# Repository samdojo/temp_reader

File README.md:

# Tempurature reader

This repo contains the schematic, code, and 3D print file to build a simple temperature reader

#### Software Dependencies
- Arduino library "adafruit_AM2320" v1.2.1

#### Materials List
- Arduino Nano
- 3 single-digit seven-segment displays (KW1-501CSB)
- Tempurature and humidity sensor (AM2320)
- 3 NPN Transistors (2N3904)
- 2 pull-up resistors (2.2-10KOhm)
- Servo (SG90)
- 4 female-to-female jumper wires
- 5 #2 1/4" screws
- glue

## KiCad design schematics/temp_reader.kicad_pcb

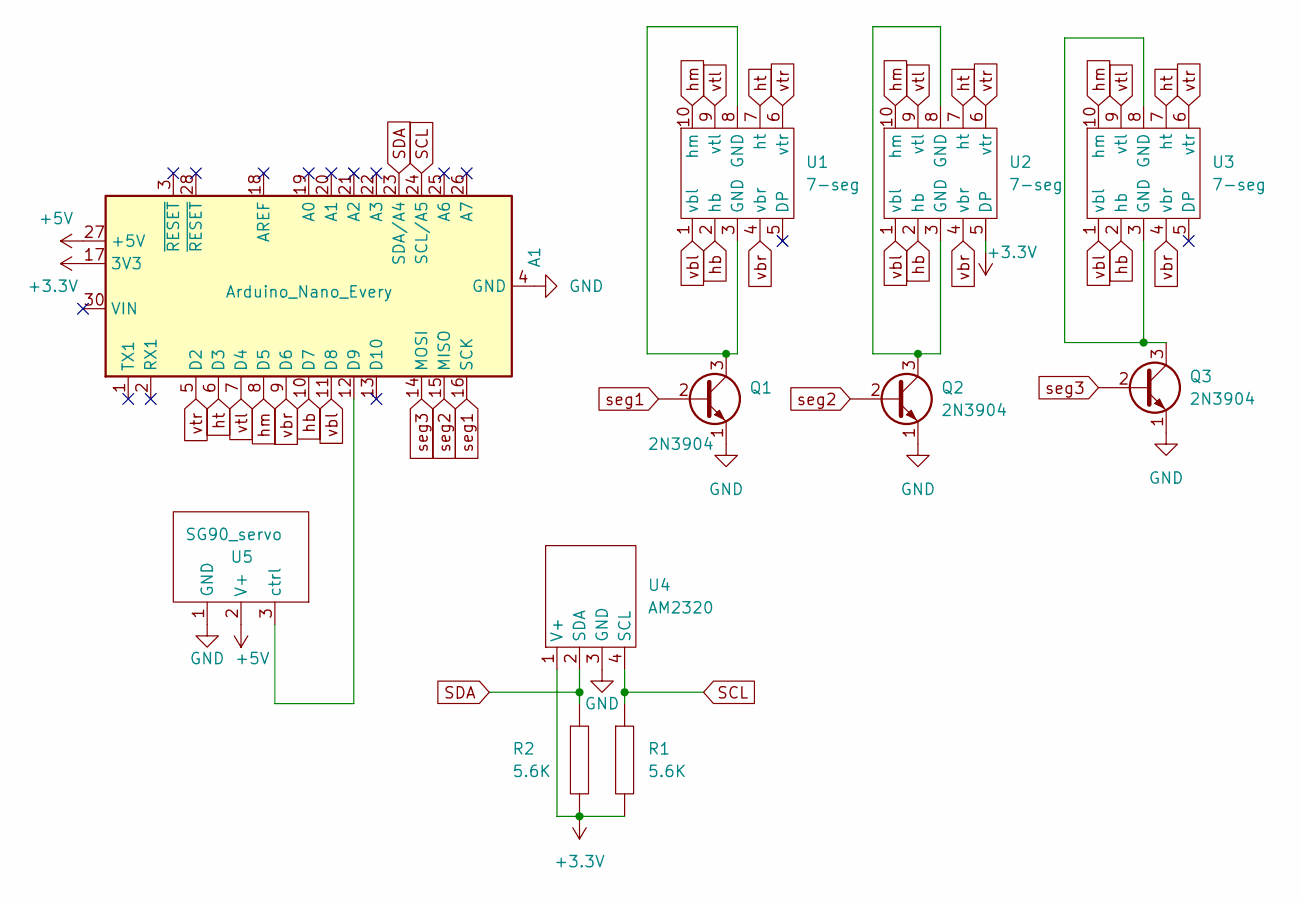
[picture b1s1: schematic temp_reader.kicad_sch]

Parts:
A1: Arduino_Nano_Every; Arduino_Nano
Q1, Q2, Q3: 2N3904; TO-92_Inline
R1, R2: 5.6K; resistor
U1, U2, U3: 7-seg; 7SegmentLED_LTS6760_LTS6780
U4: AM2320; AM2320 (temperature and humidity sensor)
U5: SG90_servo; MG90S servo

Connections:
+3.3V: A1.17 (3V3), R1.2, R2.2, U2.5 (DP), U4.1 (V+)
+5V: A1.27 (+5V), U5.2 (V+)
GND: A1.4 (GND), A1.29 (GND), Q1.1 (E), Q2.1 (E), Q3.1 (E), U4.3 (GND), U5.1 (GND)
unnamed: A1.12 (D9), U5.3 (ctrl)
unnamed: Q1.3 (C), U1.3 (GND), U1.8 (GND)
unnamed: Q2.3 (C), U2.3 (GND), U2.8 (GND)
unnamed: Q3.3 (C), U3.3 (GND), U3.8 (GND)
SCL: A1.24 (SCL/A5), R1.1, U4.4 (SCL)
SDA: A1.23 (SDA/A4), R2.1, U4.2 (SDA)
hb: A1.10 (D7), U1.2 (hb), U2.2 (hb), U3.2 (hb)
hm: A1.8 (D5), U1.10 (hm), U2.10 (hm), U3.10 (hm)
ht: A1.6 (D3), U1.7 (ht), U2.7 (ht), U3.7 (ht)
seg1: A1.16 (SCK), Q1.2 (B)
seg2: A1.15 (MISO), Q2.2 (B)
seg3: A1.14 (MOSI), Q3.2 (B)
vbl: A1.11 (D8), U1.1 (vbl), U2.1 (vbl), U3.1 (vbl)
vbr: A1.9 (D6), U1.4 (vbr), U2.4 (vbr), U3.4 (vbr)
vtl: A1.7 (D4), U1.9 (vtl), U2.9 (vtl), U3.9 (vtl)
vtr: A1.5 (D2), U1.6 (vtr), U2.6 (vtr), U3.6 (vtr)

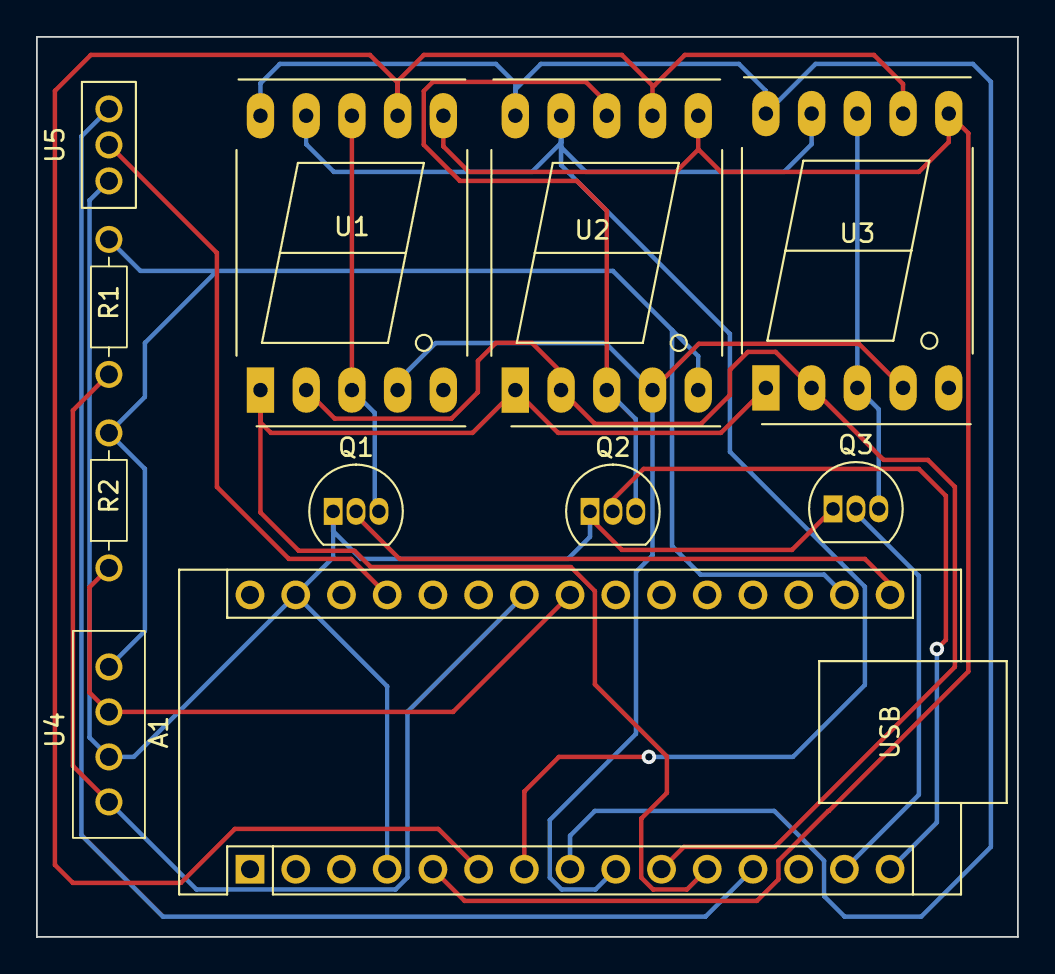
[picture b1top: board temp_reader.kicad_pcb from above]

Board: 2 copper layers, 54.5 x 50.0 mm, 11 parts (0 on the bottom side), 19 nets.

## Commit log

2023-02-24 initial
2023-02-26 added schematic picture
2023-02-26 added PCB layout picture
2023-02-26 added images of board
2023-03-15 moved src file
2023-03-18 made display class
2023-03-18 updated PCB schematic and layout
2023-03-18 renamed export files
2023-03-20 added tempurature module
2023-03-20 using 3.3v for decimal LED
2023-03-31 updated servo model and adjusted temp sensor blueprint
2023-04-03 reorganized PCB layout to move sensor farther away from displays
2023-04-03 added servo test code and fixed display bug
2023-04-03 added 3D files
2023-04-03 added materials list
2023-04-26 updated case and lid 3D models, added arm 3D model, removed test code
2023-04-28 added cool mode
2023-04-28 added materials
2023-04-28 added arm class; removed cool mode
